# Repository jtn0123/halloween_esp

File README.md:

# Halloween Castle

A store-bought decorative castle with three lit apertures — two tower windows and
a doorway — driven by an ESP32-S3 Feather running ESPHome. Addressable RGBW pixels,
pre-rendered spooky audio, and a cue engine that keeps the two in step.

See [PROJECT_NOTES.md](PROJECT_NOTES.md) for the design record and the hardware
research behind every choice here — it is an index; the record itself lives in
parts under [`docs/notes/`](docs/notes/). The trust model — local-only, two
permanently accepted risks — is [docs/SECURITY.md](docs/SECURITY.md). For the night-to-night view —
adding a song end to end, pushing to the castle, what to check when a scene
will not play — see [docs/RUNBOOK.md](docs/RUNBOOK.md).

---

## How it fits together

```
scenes/scenes.yaml            ← THE SOURCE OF TRUTH
        │
        ├── tools/render_audio.py ─▶ core/ scene_render ─▶ audio/NN_<id>.mp3
        │                            (Rust: synths, reverb,   and audio/card/
        │                             master chain)            (the 96 kbps copies)
        ├── tools/gen_esphome.py  ──▶ audio/card/scenes/      (THE SHOW: show.man
        │                         │                            + one <id>.cue a scene)
        │                         └─▶ firmware/generated/     (sfx, rig.h, lights)
        └── tools/gen_previewer.py ─▶ previewer/castle-cue-desk.html (the desk)
```

One file defines every scene: its light cues, its audio score, its length and its
playback level. Everything else is generated. Cue timings tuned in the previewer
cannot drift away from the ones on the device, because both come from here.
Since v5.67 the show is card data, not firmware: one runner
(`firmware/castle_scenes.h`) reads `show.man` and the `.cue` files, so a scene
edit is `make publish`, never a flash.

`core/` is castle-core, the project's zero-dependency Rust crate. It renders the
scene audio (`scene_render`) and analyses imported tracks (`analyze_track`) —
those are the production paths, not experiments; the Python originals survive
only as the parity references the Rust is checked against. It also holds a
WASM face the cue desk loads and the studio server itself — the only one since
the Python studio retired on 2026-09-06 ([docs/RETIREMENT.md](docs/RETIREMENT.md)).
Everything else reaches the crate through
`tools/core_bins.py`, as a subprocess: no cargo means a hard stop with a
sentence, never a quiet fall-back to arithmetic that differs per machine.

### Why the audio is pre-rendered

The MAX98357A plays one stream, and mixing on the board itself is not worth
fighting (it was never an option at all on the single-core ESP32-S2 this show
was written for). So each scene is rendered offline into a single mixed file — where
convolution reverb, ducking and crossfades are free — and the firmware's only job
is to play it. This raises the quality ceiling rather than lowering it.

---

## Hardware

The [v3.4 Integrated PCB handoff](hardware/castle-carrier-v3.4/integrated/README.md)
contains its KiCad source, ENIG manufacturing review package, board images and QA evidence.
It remains an engineering prototype pending supplier and powered-board qualification.

| | |
|---|---|
| MCU | Adafruit ESP32-S3 Feather [#5477](https://www.adafruit.com/product/5477) — 240 MHz, 4 MB flash, 2 MB PSRAM, on castle-carrier v3.3a. An ESP32-S2 Feather ran the porch until 2026-09-17 ([docs/notes/03-build.md](docs/notes/03-build.md) §12.20) |
| Audio | MAX98357A I2S class-D amp ([adafruit 3006](https://www.adafruit.com/product/3006)) → 4 Ω speaker |
| Light | 2 × NeoPixel Jewel 7 RGBW (towers) + NeoPixel Ring 12 RGB (door) — three zones, 26 pixels; see [docs/WIRING.md](docs/WIRING.md) |
| Sensor | AM312 PIR on the walkway |

I2S and RMT are separate peripherals, so audio and pixels never contend for
hardware.

### Wiring

| Feather pin | GPIO | Goes to |
|---|---|---|
| A0 | 18 | 74AHCT125 → 470 Ω → Jewel `DIN` |
| A1 | 17 | AM312 PIR out |
| A3 | 15 | MAX98357A `DIN` |
| D11 | 11 | MAX98357A `BCLK` |
| D12 | 12 | MAX98357A `LRC` |
| USB | — | 5 V to amp, pixels, level shifter |
| GND | — | common ground |

**Why not D5/D6/D10, which would be the obvious choices?** History: until
v5.44 the microSD slot came on a 2.13" eInk FeatherWing, which hard-wires SD
chip select on D5, SRAM chip select on D6, eInk chip select on D9 and eInk
data/command on D10 — and putting 800 kHz NeoPixel data on the SD card's
chip select is not a mistake you find quickly. The wing and its status
panel are gone (the page does that job now), the carrier board's own card
socket kept D5, and D6/D10 went to the carrier's 5 V sense and wired button
instead. The signals stayed where they were soldered.

Put a 1000 µF capacitor across 5 V/GND at the pixels. With 26 pixels the
worst case (a full-white lightning strike) is ~2 A, so **split the 5 V supply
before the Feather** rather than drawing it all through its USB trace.

---

## Getting started

You need Python 3.13 and **a Rust toolchain** (`rustup`, which brings cargo).
`make setup` does not install Rust, and the step after it does not work
without one: `make audio` renders through castle-core and stops with a
sentence rather than falling back to Python. Node 22+, `lame` and `ffmpeg`
are needed for `make check`; `make setup` ends by naming whichever is missing,
with the command that installs it.

```bash
curl --proto '=https' --tlsv1.2 -sSf https://sh.rustup.rs | sh   # once
make setup      # venv from the hashed lock + web/ npm ci + the commit hook
make audio      # render the scene audio (builds core/ on first use)
make validate   # check the config without a toolchain
make build      # compile firmware/castle_feather_s3.yaml — the castle in the yard
make build-s3   # compile firmware/castle_s3.yaml — the ESP32-S3-WROOM-1 carrier
make build-fs3  # an alias for build; the castle IS the S3 Feather
make upload     # flash over USB
make publish    # push the rendered show to the castle's microSD card
```

Copy `firmware/secrets.yaml.example` to `firmware/secrets.yaml` and set real
WiFi credentials before flashing. `make help` lists every target.

There are two targets because there are two boards. `castle_feather_s3.yaml`
is the ESP32-S3 Feather (#5477, the 2 MB PSRAM one) in the castle-carrier
v3.3a the S2 was drawn for — it is the castle in the yard, and has run the
show since 2026-09-17. `castle_s3.yaml` (2026-09-05) is the
ESP32-S3-WROOM-1 carrier board (castle-carrier v5), written from that
project's spec with no board in hand; it has never been on hardware and is
compiled weekly by CI so it cannot rot. Both share every line of the show and
not one GPIO number differs between them — see `firmware/pending/README.md`
for what has run on what, and the bring-up list.

The scene audio lives on the card, not in the image — `make publish` is what
puts it there, and a board flashed without it chirps instead of playing. That
used to be a choice between two builds; the show's real songs weigh 2.2 MB
and an OTA slot holds 1.75 MB, so on 2026-09-01 the all-in-flash build was
retired and the card became the only way the castle plays (`docs/notes/03-build.md`
§12.15).

When both `site/index.html.gz` and `site/index.html` are on the card, `/`
serves the gzipped copy. `make publish` / `sd_sync site` writes both; a hand
copy must include the `.gz` or a newer plain file is ignored. A PUT whose
`Content-Length` is larger than the body that arrives is a known ESP-IDF
httpd limit (the socket closes on the short read). The API server has four
open sockets (`firmware/sd_web.h`); that is the board's pool, not a desk bug.

---

## Castle Radio on your desktop

Install it with `sh installer/install.sh` on an Apple Silicon Mac, or
`installer\install.cmd` on Windows ([installer/README.md](installer/README.md)):
it brings its own Python, ffmpeg and voice model, with no Homebrew. On a Mac,
double-click **Enable Website Startup.command** once, then use **Import
music → Start Castle Tools → Connect Castle Tools** on the castle website. The helper runs in the background without Terminal; keep the small
connection window open. Startup checks tools without installing anything. [Desktop setup and limitations](demo/castle-radio/README.md).

## The cue desk

```bash
make studio     # http://127.0.0.1:8765 — the previewer plus a local server
```

The previewer is one static HTML file (`previewer/castle-cue-desk.html`, built
by `make preview` from `web/src/`). Behind it, the studio server adds what a
static page cannot do: the **Tracks** panel imports audio (a file, or a link via
yt-dlp), shows onsets and waveforms, auditions clips, writes scenes into
`scenes/scenes.yaml`, and sends files to the castle's SD card when one answers.
`--lan` opens it to the phone/iPad remote; leave it off otherwise — a LAN
visitor has the whole desk, not a read-only view: they can import and delete
tracks, rewrite `scenes/scenes.yaml`, send files to the castle and stop the
server (`POST /studio/server/stop`), with no login. The route
table — what the studio owns (`/studio/…`) and what it relays to the castle
(`/api/…`) — is [docs/API.md](docs/API.md).

The studio is `core/src/bin/studio.rs`: `make studio` runs
`tools/studio_launch.sh`, which builds the binary when cargo is present and
execs it, and says why it cannot when there is no cargo and no build. There
was a second studio in Python until 2026-09-06, kept as the reference the
Rust one was measured against; [docs/RETIREMENT.md](docs/RETIREMENT.md) is
the plan that retired it and the tag `python-studio-final` is the last tree
carrying it. The server is Rust; the toolchain it spawns for every rebuild,
import and push is still Python, and that is the design rather than a
leftover — [docs/PARITY.md](docs/PARITY.md) says what is held equal to what.

Four environment variables sandbox it: `CASTLE_TRACKS` (track library
directory), `CASTLE_SCENES` (the scenes file it may write), `CASTLE_HOST`
(the castle's address; set-but-empty means "no castle") and `CASTLE_BUILD`
(where a rebuild's audio, generated firmware and previewer page land). The
tests set them so a run can never touch the real show. `tools/castle_emu.py 8093` plus
`CASTLE_HOST=127.0.0.1:8093` gives the whole desk→studio→castle chain with no
hardware at all.

---

## Development

```bash
make test       # python unit tests         make lint   # ruff + mypy
make check      # tests + lint + guards + tsc + node suites (what CI runs)
make e2e        # Playwright against the real studio (CASTLE_E2E_PORT=8821 to run two)
make coverage   # non-gating coverage report     make audit  # pip-audit, non-gating
```

The five implementations of the show's arithmetic (Python generators, TS
effects, C++ firmware, host-compiled dump, and castle-core in `core/`) are kept
bit-exact by seeded fuzz — [docs/PARITY.md](docs/PARITY.md) is the contract, the
list of every duplicated copy, and what to do when one of them goes red.
`make rust` builds the crate's binaries; `make rust-test` and `make rust-lint`
(fmt --check + clippy -D warnings) are the crate's own gates, and the same
checks ride inside `tests/test_castle_core.py` so `make check` covers `core/`
too — but only on a machine that has cargo and a host C++ compiler.
`make rust-coverage` is the crate's `cargo llvm-cov` summary, non-gating like
`make coverage`.

Every file is held to 500 lines (`tools/check_loc.py`, prose included).
`make setup` installs the commit hook (`git config core.hooksPath githooks`).
A git worktree needs its own `.venv` and `web/node_modules`, or symlinks back
to the main checkout's. The short version of all of this is
[CONTRIBUTING.md](CONTRIBUTING.md).

---

## Scenes

| Scene | Kind | Length | What happens |
|---|---|---|---|
| Vigil | ambient, loops | 30 s | Candles breathe, ember at the door, wind underneath |
| Storm | triggered | 6.5 s | Thunder first, strike 80 ms behind, rolling flashes |
| Séance | ambient, loops | 35 s | Organ procession i–♭II–i–V7♭9, violet with green wisps |
| Ballroom | ambient, loops | 15 s | Parlour waltz, music box over piano, violet↔green drift |
| Descent | showpiece | 27 s | 32′ pedal held throughout, chromatic descent, strikes on chord changes |
| Visitation | triggered | 11 s | Candles gutter out, cold green, eyes open in the left window |
| Approach | PIR | 8 s | Blackout, a beat of nothing, then the door blazes |
| Crypt | ambient, loops | 24 s | Heartbeat at 48 bpm, tritone drone, whispers; near-darkness is the effect |

Imported songs take the rest of the budget: the board holds **12 scenes**
(`SCENE_LIMIT` in `tools/check_loc.py`, and the desk refuses the thirteenth),
so the eight written above leave four slots for tracks brought in through the
Tracks panel, whose cues are onset-detected from the audio itself. Two of
those four are filled in `scenes/scenes.yaml` today.

All musical material written for the castle is original, written in the haunted-parlour idiom
(minor key, 3/4 or slow chords, raised 7th on the dominant). Nothing is a
transcription of an existing work.

### Effect vocabulary

`candle` · `ember` · `furnace` · `spirit` · `eyes` · `seance` · `wisp` ·
`mansion` · `chill` · `throb` · `strobe` · `off`, plus a global `strike` overlay.

Defined in [firmware/castle_effects.h](firmware/castle_effects.h). Flicker runs on
smoothed value noise, and the seed varies per pixel so flame moves *across* a
jewel rather than the whole window pulsing as one lamp.

---

## Safety

`Soften lightning` defaults **on**. Hard ~7 Hz white strobe sits in the
photosensitive seizure band, which matters for anything pointed at a public
walkway. Turning it off is a deliberate act. Since firmware v5.71 it acts on
flash TRAINS only: a strike is softened when it lands on a zone less than
333 ms after that same zone's previous strike (faster than three a second);
an isolated strike, or a steady beat on each fixture, lands at full strength.
The soft strobe effect is unchanged. The rule is `castle_layers.h`
`kSoftenWindowMs`, mirrored by the desk and the Radio (docs/PARITY.md).

---

## Licence

This repository's code is under the MIT License: see [LICENSE](LICENSE). A
built firmware image also contains GPL-3.0 components, ESPHome's C++ runtime
and esp-audio-libs, so an image is distributed as a whole under the GNU
General Public License version 3. [docs/LICENSING.md](docs/LICENSING.md) says
what each published artifact contains, under which terms, and where its
third-party notices are.

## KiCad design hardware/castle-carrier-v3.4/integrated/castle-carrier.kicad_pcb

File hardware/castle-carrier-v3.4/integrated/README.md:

# Castle v3.4 Integrated — Mac handoff

Open `castle-carrier.kicad_pro` with **KiCad 10.0.6 or newer KiCad 10**.
This is the Integrated N16R8 prototype: 16 MB flash, 8 MB octal PSRAM,
SD storage and directly mounted LEFT/RIGHT MAX98357A amplifiers.
The native PCB is authoritative; historical bootstrap scripts cannot recreate all final edits.

## Continue on another Mac

From a checkout of `jtn0123/halloween_esp`, run
`gh pr checkout pcb/v34-integrated-enig-handoff` or check out that remote branch with Git.
Open the project in `hardware/castle-carrier-v3.4/integrated/`.
Install the standard KiCad 10 symbols, footprints and 3D models, and initialize
its standard global library tables when prompted. Custom libraries and simplified
connector/button models are included. Project tables use KiCad environment variables
instead of the old USB application path.

Run `bash validate.sh` here for package integrity, ENIG agreement, the 16-hole list,
fresh DRC with schematic parity and ERC. Set `KICAD_CLI` if KiCad is outside
`/Applications/KiCad/KiCad.app` and not on PATH. Reports go to ignored `local-checks/`.
This focused check does not reproduce the original two-variant engineering QA suite.

## Manufacturing decision

- ENIG, 1 microinch gold; four layers, 1.6 mm FR-4 TG135;
  1 oz outer / 0.5 oz inner copper.
- Exactly 16 epoxy-filled, planarized, copper-capped thermal holes:
  12 beneath the ESP32 module and two beneath each amplifier.
- JLC Standard assembly and X-ray; five boards, two assembled and three bare.
- Red or black remains an order choice. Intended supply: regulated 5 V / 4 A
  barrel adapter. The board is 100 × 80 mm.

Read [assembly notes](ASSEMBLY-NOTES.md) and
[current requirements](docs/ASSEMBLY-REQUIREMENTS.md).
Unzip [the manufacturing package](out/DFM_REVIEW_NOT_RELEASED.zip) and read
`READ-ME-FIRST.md`. It contains Gerbers, drills, engineering BOM, a placement
reference and the thermal-hole map. It remains **review only, not released**;
placement data and CAD paste layers require assembler approval.

## Current readiness

The October 7 follow-up fixes the clean-checkout validator, refreshes Integrated compilation against application commit 3078e35, and tunes both USB-C contact paths to about 0.795 mm mismatch (target <=1 mm). The revised native PCB passed refilled DRC/parity with no violations or disconnected items. The 100 x 80 mm outline, component placement, finish and 16-hole process stay the same.

C20/C21/C24/C25 now select Samsung CL10C221JB8NNNC / C27675 after comparing electrical specs and dimensions with the out-of-stock Murata part. The engineering BOM and manufacturing ZIP agree. [Stock evidence](qa/jlc-stock-20261007.json) is a dated public-page snapshot, not reserved inventory. The fuse cartridge remains a separately installed exact-MPN item.

See [readiness findings](docs/READINESS-20261007.md), [dimensioned fit drawing](out/fit-dimensions.pdf), [supplier review request](docs/SUPPLIER-REVIEW.md), and [first-board procedure](docs/FIRST-ARTICLE-TEST.md). The only given mechanical constraint is the 80-82 mm PCB-width cap; no enclosure model is assumed. The RF clearance outside the PCB is not a component body.

The [firmware overlay](firmware-reference/castle_v34.yaml) now has a [portable compilation workflow](firmware-reference/README.md), with [current build evidence](qa/firmware-build-20261007.json). Compilation is not physical playback or detected-memory proof. Printed v3.3a keeps its existing mono profile.

The archived receipt `20261002T012938Z-df738972` describes the earlier USB workspace and is historical; it does not qualify the revised USB copper or current application firmware. Keep [the archive](qa/20261002T012938Z-df738972-evidence.zip) and [ENIG source patch](qa/enig-source-update.patch) as history. The new report records fresh checks separately. The portable import manifest hashes published files, excluding KiCad local settings.

Supplier CAM/stock/orientation/stencil acceptance and powered USB, stereo, SD, combined-load/thermal and RF tests remain open. This is a prototype handoff, not a production release. No order, supplier submission, device flash or physical test was performed.

## Board views

These are CAD images. Component positions remain unchanged; current copper views include the USB correction.

More top, bottom, angled, schematic and mechanical views are in `renders/` and `out/`.

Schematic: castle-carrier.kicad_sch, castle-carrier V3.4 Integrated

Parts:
C1, C2, C6, C11, C14, C17, C18, C22: 100nF; C_0603_1608Metric
C3: 10uF 16V; CP_Radial_D6.3mm_P2.50mm
C4: 1000uF 16V; CP_Radial_D10.0mm_P5.00mm
C5: 470uF 16V; CP_Radial_D8.0mm_P3.50mm
C7, C8, C19, C23: 10uF 25V; C_0805_2012Metric
C9, C10, C13: 22uF 25V; C_0805_2012Metric
C15: 1uF; C_0603_1608Metric
C16, C26: 1uF 25V; C_0805_2012Metric
C20, C21, C24, C25: 220pF; C_0603_1608Metric
D1: SS56C; D_SMC
D3: SMBJ6.8A; D_SMB
D4: amber; LED_1206_3216Metric
D5: 12V zener; D_SOD-123
D6, D7: B5819W; D_SOD-123
F1: 4A 5x20; Fuseholder_5x20_BLX-A
FB1, FB2, FB3, FB4: BLM21PG221SN1D; L_0805_2012Metric
H1, H2, H3, H4: M3; MountingHole_3.2mm_M3
J1, J2, J3, J4: PT 3.5 1x03; TerminalBlock_Phoenix_PT-1,5-3-3.5-H_1x03_P3.50mm_Horizontal
J5: AM312 PIR; JST_XH_B3B-XH-A_1x03_P2.50mm_Vertical
J7: SPEAKER L; TerminalBlock_Phoenix_PT-1,5-2-3.5-H_1x02_P3.50mm_Horizontal
J8: SPEAKER R; TerminalBlock_Phoenix_PT-1,5-2-3.5-H_1x02_P3.50mm_Horizontal
J9: DM3AT-SF-PEJM5; microSD_HC_Hirose_DM3AT-SF-PEJM5
J10: DEBUG UART; PinHeader_1x05_P2.54mm_Vertical
J11: DC-005-5A; DC-005
J12: BTN + PIXEL; JST_XH_B4B-XH-A_1x04_P2.50mm_Vertical
J15: QWIIC I2C; JST_SH_SM04B-SRSS-TB_1x04-1MP_P1.00mm_Horizontal
J16: TYPE-C-31-M-12; USB_C_Receptacle_HRO_TYPE-C-31-M-12
L1: 4.7uH; L_Sunlord_SWPA6045S
Q1: AOD4185; TO-252-3_TabPin2
R1, R2, R3, R4: 100R; R_1206_3216Metric
R5, R6, R7, R8, R9, R10, R11: 10k; R_1206_3216Metric
R12: 4k7; R_Axial_DIN0207_L6.3mm_D2.5mm_P7.62mm_Horizontal
R13: 10k; R_Axial_DIN0207_L6.3mm_D2.5mm_P7.62mm_Horizontal
R14, R17, R18, R31, R32: 10k; R_0603_1608Metric
R19: 100R; R_0603_1608Metric
R20: 1k; R_0603_1608Metric
R21: 10mR; R_2512_6332Metric
R22, R23: 5k1; R_0603_1608Metric
R24, R25: 4k7; R_0603_1608Metric
R26, R27, R28: 33R; R_0603_1608Metric
R29: 100k; R_0603_1608Metric
R30: 374k; R_0603_1608Metric
SW1: OS102011MS2Q; SW_Slide_SPDT_CK_OS102011MS2Q
SW2: BOOT; SW_Push_1P1T_XKB_TS-1187A
SW3: RESET; SW_Push_1P1T_XKB_TS-1187A
TP1: +5V; TestPoint_Pad_D1.5mm
TP2: +3V3; TestPoint_Pad_D1.5mm
TP3: GND; TestPoint_Pad_D1.5mm
TP4: TOWERL; TestPoint_Pad_D1.5mm
TP5: DOOR; TestPoint_Pad_D1.5mm
TP6: TOWERR; TestPoint_Pad_D1.5mm
TP7: SPARE; TestPoint_Pad_D1.5mm
TP8: VBUS; TestPoint_Pad_D1.5mm
U1: 74AHCT125; SOIC-14_3.9x8.7mm_P1.27mm
U2: ESP32-S3-WROOM-1-N16R8; ESP32-S3-WROOM-1
U3: AP63203WU-7; TSOT-23-6
U4: USBLC6-2SC6; SOT-23-6
U5: INA219AIDCNR; SOT-23-8
U6, U7: MAX98357AETE+T; MAX98357A_TQFN16_3x3
U8: TPS22919DCKR; SOT-363_SC-70-6

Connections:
+3V3: C2.1, C3.1, C7.1, C9.1, C10.1, C13.1, C14.1, C17.1, J5.1 (3V3), J9.4 (VDD), J15.2 (3V3), L1.2, R5.1, R6.1, R7.1, R13.1, R17.1, R18.1, R24.1, R25.1, R31.1, R32.1, TP2.1, U2.2 (3V3), U3.1 (FB), U5.4 (VS), U5.7 (A0)
+5V: C1.1, C4.1, C5.1, C18.1, C19.1, C22.1, C23.1, D1.1 (K), D3.1 (K), D7.2 (A), J1.1 (5V), J2.1 (5V), J3.1 (5V), J4.1 (5V), J10.1 (5V), J12.1 (5V), R12.1, R21.2 (OUT), R29.1, R30.1, TP1.1, U1.14 (VCC), U5.2 (IN-), U6.7 (VDD), U6.8 (VDD), U7.7 (VDD), U7.8 (VDD)
/AUD_L_MODE: R29.2, U6.4 (SD_MODE)
/AUD_L_N: FB2.1, U6.10 (OUTN)
/AUD_L_P: FB1.1, U6.9 (OUTP)
/AUD_L_SPK_N: C21.1, FB2.2, J7.2 (SPK-)
/AUD_L_SPK_P: C20.1, FB1.2, J7.1 (SPK+)
/AUD_R_MODE: R30.2, U7.4 (SD_MODE)
/AUD_R_N: FB4.1, U7.10 (OUTN)
/AUD_R_P: FB3.1, U7.9 (OUTP)
/AUD_R_SPK_N: C25.1, FB4.2, J8.2 (SPK-)
/AUD_R_SPK_P: C24.1, FB3.2, J8.1 (SPK+)
/BOOT0: R18.2, SW2.1, U2.27 (IO0)
/BST_BUCK: C11.1, U3.6 (BST)
/CC1: J16.A5 (CC1), R22.1
/CC2: J16.B5 (CC2), R23.1
/GATE_P: D5.2 (A), Q1.1 (G), R14.1
/LED_A: D4.2 (A), SW1.1 (A)
/PWR_LED: R12.2, SW1.2 (B)
/RST_BTN: R19.1, SW3.2
/RST_J10: J10.5 (RST), R20.1
/SHUNT_5V: D5.1 (K), Q1.3 (S), R21.1 (IN), U5.1 (IN+)
/SW_BUCK: C11.2, L1.1, U3.5 (SW)
/VIN_F: F1.2, Q1.2 (D)
/VIN_RAW: F1.1, J11.1 (CENTRE_+)
/Y1: R1.2, U1.3 (1Y)
/Y2: R2.2, U1.6 (2Y)
/Y3: R3.2, U1.8 (3Y)
/Y4: R4.2, U1.11 (4Y)
BTN: C6.1, J12.3 (BTN), R13.2, U2.18 (IO10)
CHIP_EN: C15.1, R17.2, R20.2, SW3.1, U2.3 (EN)
DBG_RX: J10.3 (RX), U2.36 (RXD0)
DBG_TX: J10.4 (TX), U2.37 (TXD0)
DOOR: J2.3 (DATA), R2.1, TP5.1
DOOR_3V3: R9.1, U1.5 (2A), U2.9 (IO16)
GND: C1.2, C2.2, C3.2, C4.2, C5.2, C6.2, C7.2, C8.2, C9.2, C10.2, C13.2, C14.2, C15.2, C16.2, C17.2, C18.2, C19.2, C20.2, C21.2, C22.2, C23.2, C24.2, C25.2, C26.2, D1.2 (A), D3.2 (A), D4.1 (K), J1.2 (GND), J2.2 (GND), J3.2 (GND), J4.2 (GND), J5.3 (GND), J9.6 (VSS), J9.SH (SHIELD), J10.2 (GND), J11.2 (SLEEVE), J11.3 (SW), J12.2 (GND), J15.1 (GND), J15.MP, J16.A1 (GND), J16.A12 (GND), J16.B1 (GND), J16.B12 (GND), J16.SH (SHIELD), R8.2, R9.2, R10.2, R11.2, R14.2, R19.2, R22.2, R23.2, SW2.2, TP3.1, U1.1 (1OE), U1.4 (2OE), U1.7 (GND), U1.10 (3OE), U1.13 (4OE), U2.1 (GND), U2.40 (GND), U2.41 (EPAD), U3.4 (GND), U4.2 (GND), U5.3 (GND), U5.8 (A1), U6.3 (GND), U6.11 (GND), U6.15 (GND), U6.17 (EP), U7.3 (GND), U7.11 (GND), U7.15 (GND), U7.17 (EP), U8.2 (GND)
I2S_BCLK: R26.1, U2.19 (IO11)
I2S_BCLK_A: R26.2, U6.16 (BCLK), U7.16 (BCLK)
I2S_DIN: R28.1, U2.8 (IO15)
I2S_DIN_A: R28.2, U6.1 (DIN), U7.1 (DIN)
I2S_LRC: R27.1, U2.20 (IO12)
I2S_LRC_A: R27.2, U6.14 (LRCLK), U7.14 (LRCLK)
PIR_OUT: J5.2 (OUT), U2.10 (IO17)
SCL: J15.4 (SCL), R25.2, U2.38 (IO2), U5.5 (SCL)
SDA: J15.3 (SDA), R24.2, U2.39 (IO1), U5.6 (SDA)
SD_CS: J9.2 (CD/DAT3), R5.2, U2.5 (IO5)
SD_DAT1: J9.8 (DAT1), R32.2
SD_DAT2: J9.1 (DAT2), R31.2
SD_MISO: J9.7 (DAT0), R7.2, U2.34 (IO41)
SD_MOSI: J9.3 (CMD), R6.2, U2.32 (IO39)
SD_SCK: J9.5 (CLK), U2.33 (IO40)
SPARE: J4.3 (DATA), J12.4 (DAT), R4.1, TP7.1
SPARE_3V3: R11.1, U1.12 (4A), U2.12 (IO8)
TOWERL: J1.3 (DATA), R1.1, TP4.1
TOWERL_3V3: R8.1, U1.2 (1A), U2.11 (IO18)
TOWERR: J3.3 (DATA), R3.1, TP6.1
TOWERR_3V3: R10.1, U1.9 (3A), U2.22 (IO14)
USB_DM: J16.A7 (D-), J16.B7 (D-), U2.13 (USB_D-), U4.3 (I/O2), U4.4 (I/O2)
USB_DP: J16.A6 (D+), J16.B6 (D+), U2.14 (USB_D+), U4.1 (I/O1), U4.6 (I/O1)
USB_SOFT: D6.2 (A), U8.6 (OUT)
VBUCK: C8.1, D6.1 (K), D7.1 (K), U3.2 (EN), U3.3 (VIN)
VBUS: C16.1, C26.1, J16.A4 (VBUS), J16.A9 (VBUS), J16.B4 (VBUS), J16.B9 (VBUS), TP8.1, U4.5 (VBUS), U8.1 (IN), U8.3 (ON)

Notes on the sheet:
POWER J11 -> F1 -> VIN_F; D1 clamp + D3 TVS + C4 on the protected +5V
POWER INDICATOR +5V -> R12 -> SW1 -> D4
MODULE SUPPLY the datasheet's own C1 = 22uF and C3 = 100nF at U2 pin 2
BOOT / RESET / EN NO CAP EVER ON BOOT0
DEBUG 3V3 UART, 5 V on PIN 1, EN via R20
TEST POINTS bare 1.5 mm pads, probe from the top
LEVEL SHIFT + ZONES 3.3 V in, 5 V out, 100R in series
STORAGE microSD, SPI, REQUIRED
SENSOR + I2C AM312 PIR, and J15 for a Qwiic device beside the on-board sensor
BUTTON wired switch on D10 + one pixel on SPARE
3V3 D6 / D7 OR USB VBUS and the barrel into VBUCK; U3 makes the ONE 3.3 V rail from it
AMMETER R21 10mOhm in series in the 5 V trunk, U5 across it at 0x41, and the I2C pull-ups
USB native, no bridge chip: two CC pull-downs, a USBLC6-2SC6 the pair passes THROUGH, 1uF VBUS
AUDIO: two on-board MAX98357A; LEFT / RIGHT stereo; 9 dB; floating speaker outputs
PROTECT: Q1 permanently in series; no bypass; 5 V supply ONLY
MCU: ESP32-S3-WROOM-1-N16R8; 16 MB flash / 8 MB octal PSRAM
I2S: 33R source damping; not a power isolation device
USB STARTUP: controlled rise; QOD disabled; D6 blocks barrel backfeed
SD: unused DAT1 / DAT2 require 10k pull-ups too
v3.4 engineering prototype - NOT RELEASED FOR MANUFACTURE
5 V center-positive supply only. TVS is not a DC overvoltage cutoff.
No speaker terminal may connect to ground or another output.
USB powers logic only; lights and amplifiers require barrel supply.

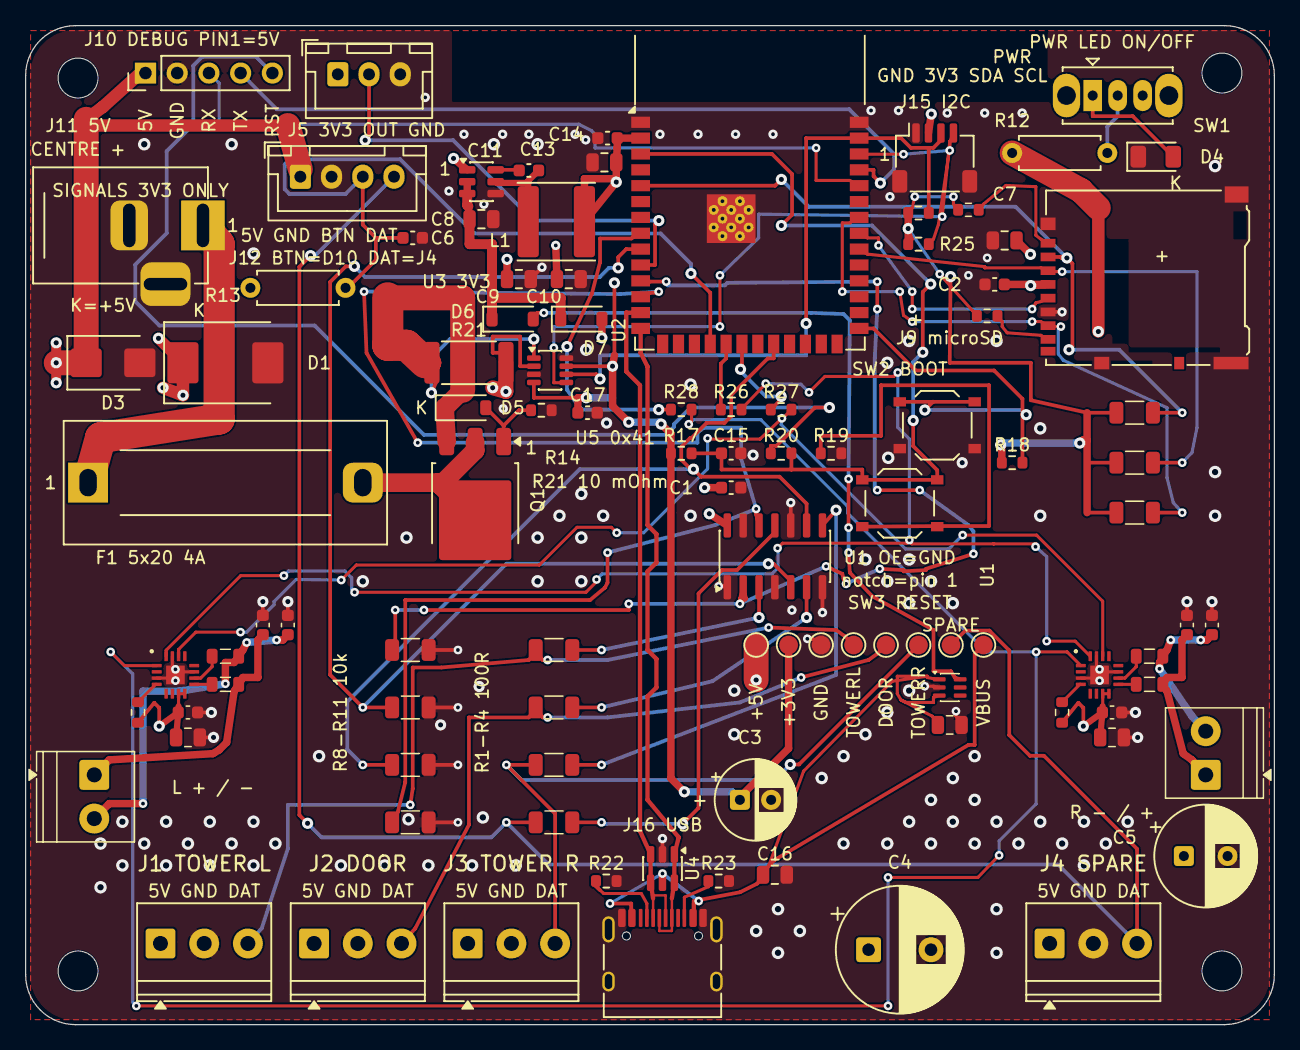
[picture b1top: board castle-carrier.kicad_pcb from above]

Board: 4 copper layers, 100.0 x 80.0 mm, 104 parts (0 on the bottom side), 62 nets.

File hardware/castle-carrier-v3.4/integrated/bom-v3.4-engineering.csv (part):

Reference,Value / MPN,Footprint,LCSC part,Sourcing status,Manufacturer,Selected MPN,Requirements,Source
U2,ESP32-S3-WROOM-1-N16R8,castle:ESP32-S3-WROOM-1,C2913202,"Exact MPN selected; source by MPN, no unreviewed substitutions",Espressif,ESP32-S3-WROOM-1-N16R8,16 MB flash / 8 MB octal PSRAM; module exposed-pad process per fabrication notes; matching Integrated firmware required,https://www.espressif.com/sites/default/files/documentation/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
U1,74AHCT125,castle:SOIC-14_3.9x8.7mm_P1.27mm,C155176,Inherited v5 selection; reconfirm before ordering,,,,
J1,PT 3.5 1x03,"TerminalBlock_Phoenix:TerminalBlock_Phoenix_PT-1,5-3-3.5-H_1x03_P3.50mm_Horizontal",C474893,Inherited v5 selection; reconfirm before ordering,,,,
J2,PT 3.5 1x03,"TerminalBlock_Phoenix:TerminalBlock_Phoenix_PT-1,5-3-3.5-H_1x03_P3.50mm_Horizontal",C474893,Inherited v5 selection; reconfirm before ordering,,,,
J3,PT 3.5 1x03,"TerminalBlock_Phoenix:TerminalBlock_Phoenix_PT-1,5-3-3.5-H_1x03_P3.50mm_Horizontal",C474893,Inherited v5 selection; reconfirm before ordering,,,,
J4,PT 3.5 1x03,"TerminalBlock_Phoenix:TerminalBlock_Phoenix_PT-1,5-3-3.5-H_1x03_P3.50mm_Horizontal",C474893,Inherited v5 selection; reconfirm before ordering,,,,
R1,100R,Resistor_SMD:R_1206_3216Metric,C137392,"Exact MPN selected; source by MPN, no unreviewed substitutions",Yageo,RC1206FR-07100RL,"100 ohm, 1%, 1206, 0.25 W at 70 C",https://www.yageogroup.com/component-documentation/download/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
R2,100R,Resistor_SMD:R_1206_3216Metric,C137392,"Exact MPN selected; source by MPN, no unreviewed substitutions",Yageo,RC1206FR-07100RL,"100 ohm, 1%, 1206, 0.25 W at 70 C",https://www.yageogroup.com/component-documentation/download/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
R3,100R,Resistor_SMD:R_1206_3216Metric,C137392,"Exact MPN selected; source by MPN, no unreviewed substitutions",Yageo,RC1206FR-07100RL,"100 ohm, 1%, 1206, 0.25 W at 70 C",https://www.yageogroup.com/component-documentation/download/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
R4,100R,Resistor_SMD:R_1206_3216Metric,C137392,"Exact MPN selected; source by MPN, no unreviewed substitutions",Yageo,RC1206FR-07100RL,"100 ohm, 1%, 1206, 0.25 W at 70 C",https://www.yageogroup.com/component-documentation/download/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
R8,10k,Resistor_SMD:R_1206_3216Metric,C132649,"Exact MPN selected; source by MPN, no unreviewed substitutions",Yageo,RC1206FR-0710KL,"10 kohm, 1%, 1206, 0.25 W at 70 C",https://www.yageogroup.com/component-documentation/download/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
R9,10k,Resistor_SMD:R_1206_3216Metric,C132649,"Exact MPN selected; source by MPN, no unreviewed substitutions",Yageo,RC1206FR-0710KL,"10 kohm, 1%, 1206, 0.25 W at 70 C",https://www.yageogroup.com/component-documentation/download/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
R10,10k,Resistor_SMD:R_1206_3216Metric,C132649,"Exact MPN selected; source by MPN, no unreviewed substitutions",Yageo,RC1206FR-0710KL,"10 kohm, 1%, 1206, 0.25 W at 70 C",https://www.yageogroup.com/component-documentation/download/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
R11,10k,Resistor_SMD:R_1206_3216Metric,C132649,"Exact MPN selected; source by MPN, no unreviewed substitutions",Yageo,RC1206FR-0710KL,"10 kohm, 1%, 1206, 0.25 W at 70 C",https://www.yageogroup.com/component-documentation/download/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
C1,100nF,castle:C_0603_1608Metric,C14663,Inherited v5 selection; reconfirm before ordering,,,,
C5,470uF 16V,Capacitor_THT:CP_Radial_D8.0mm_P3.50mm,C1579437,Inherited v5 selection; reconfirm before ordering,,,,
R26,33R,castle:R_0603_1608Metric,C108661,"Exact MPN selected; source by MPN, no unreviewed substitutions",Yageo,RC0603FR-0733RL,"33 ohm, 1%, 0603, 0.1 W",https://www.yageogroup.com/component-documentation/download/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
R27,33R,castle:R_0603_1608Metric,C108661,"Exact MPN selected; source by MPN, no unreviewed substitutions",Yageo,RC0603FR-0733RL,"33 ohm, 1%, 0603, 0.1 W",https://www.yageogroup.com/component-documentation/download/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
R28,33R,castle:R_0603_1608Metric,C108661,"Exact MPN selected; source by MPN, no unreviewed substitutions",Yageo,RC0603FR-0733RL,"33 ohm, 1%, 0603, 0.1 W",https://www.yageogroup.com/component-documentation/download/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
J9,DM3AT-SF-PEJM5,Connector_Card:microSD_HC_Hirose_DM3AT-SF-PEJM5,C114218,"Exact MPN selected; source by MPN, no unreviewed substitutions",Hirose,DM3AT-SF-PEJM5,MicroSD push/push socket; native footprint; installed-height and insertion/ejection fit remain physical gates,https://www.hirose.com/product/p/CL0609-0031-0-00
R5,10k,Resistor_SMD:R_1206_3216Metric,C132649,"Exact MPN selected; source by MPN, no unreviewed substitutions",Yageo,RC1206FR-0710KL,"10 kohm, 1%, 1206, 0.25 W at 70 C",https://www.yageogroup.com/component-documentation/download/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
R6,10k,Resistor_SMD:R_1206_3216Metric,C132649,"Exact MPN selected; source by MPN, no unreviewed substitutions",Yageo,RC1206FR-0710KL,"10 kohm, 1%, 1206, 0.25 W at 70 C",https://www.yageogroup.com/component-documentation/download/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
R7,10k,Resistor_SMD:R_1206_3216Metric,C132649,"Exact MPN selected; source by MPN, no unreviewed substitutions",Yageo,RC1206FR-0710KL,"10 kohm, 1%, 1206, 0.25 W at 70 C",https://www.yageogroup.com/component-documentation/download/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
C2,100nF,castle:C_0603_1608Metric,C14663,Inherited v5 selection; reconfirm before ordering,,,,
C7,10uF 25V,castle:C_0805_2012Metric,C15850,"Exact MPN selected; source by MPN, no unreviewed substitutions",Samsung,CL21A106KAYNNNE,"10 uF 25 V X5R 0805; assess effective capacitance at bias, tolerance and temperature; nominal capacitance is not proof",https://product.samsungsem.com/mlcc/CL21A106KAYNNN.do
C3,10uF 16V,Capacitor_THT:CP_Radial_D6.3mm_P2.50mm,C2835646,Inherited v5 selection; reconfirm before ordering,,,,
J5,AM312 PIR,Connector_JST:JST_XH_B3B-XH-A_1x03_P2.50mm_Vertical,C144394,Inherited v5 selection; reconfirm before ordering,,,,
J12,BTN + PIXEL,Connector_JST:JST_XH_B4B-XH-A_1x04_P2.50mm_Vertical,C144395,Inherited v5 selection; reconfirm before ordering,,,,
R13,10k,Resistor_THT:R_Axial_DIN0207_L6.3mm_D2.5mm_P7.62mm_Horizontal,C5618323,Inherited v5 selection; reconfirm before ordering,,,,
C6,100nF,castle:C_0603_1608Metric,C14663,Inherited v5 selection; reconfirm before ordering,,,,
J10,DEBUG UART,castle:PinHeader_1x05_P2.54mm_Vertical,C492404,Inherited v5 selection; reconfirm before ordering,,,,
J15,QWIIC I2C,castle:JST_SH_SM04B-SRSS-TB_1x04-1MP_P1.00mm_Horizontal,C160404,Inherited v5 selection; reconfirm before ordering,,,,
J11,DC-005-5A,castle:DC-005,C381116,Inherited v5 selection; reconfirm before ordering,,,,
F1,4A 5x20,castle:Fuseholder_5x20_BLX-A,C3131,"Exact MPN selected; source by MPN, no unreviewed substitutions",Xucheng,5x20 BLX-A XC-7,"Holder only, rated 6.3 A; fit one separately listed F1-CARTRIDGE",https://www.lcsc.com/product-detail/C3131.html
D1,SS56C,castle:D_SMC,C24138,Inherited v5 selection; reconfirm before ordering,,,,
Q1,AOD4185,castle:TO-252-3_TabPin2,C400894,Inherited v5 selection; reconfirm before ordering,,,,
R14,10k,castle:R_0603_1608Metric,C25804,Inherited v5 selection; reconfirm before ordering,,,,
D5,12V zener,castle:D_SOD-123,C500776,Inherited v5 selection; reconfirm before ordering,,,,
C4,1000uF 16V,Capacitor_THT:CP_Radial_D10.0mm_P5.00mm,C2166071,Inherited v5 selection; reconfirm before ordering,,,,
D3,SMBJ6.8A,castle:D_SMB,C152090,Inherited v5 selection; reconfirm before ordering,,,,
U3,AP63203WU-7,castle:TSOT-23-6,C780769,"Exact MPN selected; source by MPN, no unreviewed substitutions",Diodes Incorporated,AP63203WU-7,"Fixed 3.3 V buck; 2 A component rating, not an assembled-board rating; TSOT26",https://www.diodes.com/assets/Datasheets/AP63200-AP63201-AP6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
L1,4.7uH,castle:L_Sunlord_SWPA6045S,C78804,"Exact MPN selected; source by MPN, no unreviewed substitutions",Sunlord,SWPA6045S4R7MT,"4.7 uH +/-20%; 6.0 +/-0.3 mm body, 4.5 mm max height; 34 milliohm max DCR; catalog Isat 4.97 A / Irms 3.30 A (columns headed Max); board current/thermal qualification remains open",https://www.sunlordinc.com/uploads/files/20221122/SWPA%20ser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

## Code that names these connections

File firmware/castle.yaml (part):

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  # renumbers nothing else. docs/WIRING.md §1-2. A2 and A4 were the pins left
  # free beside the eInk wing; GPIO16 is safe for the same reason GPIO15 is —
  # this board fits no 32 kHz crystal.
  pin_towerL: "18"      # A0  -> 74AHCT125 1Y -> 470R -> tower L DIN
  pin_door: "16"        # A2  -> 74AHCT125 2Y -> 470R -> doorway DIN
  pin_towerR: "14"      # A4  -> 74AHCT125 3Y -> 470R -> tower R DIN
  # Pixel count and colour type per zone. These MUST agree with the `zones:`
  # block in scenes/scenes.yaml — that is what the cue scripts and the
  # geometry tables in generated/rig.h were built against.
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  channels_door: "GRB"
  pin_pir: "17"         # A1  <- AM312 PIR out (3V3 logic)
  pin_i2s_dout: "15"    # A3  -> MAX98357A DIN
  pin_i2s_bclk: "11"    # D11 -> MAX98357A BCLK   (clear of the wing)
  pin_i2s_lrclk: "12"   # D12 -> MAX98357A LRC    (clear of the wing)
  # Both amps sit on those same three wires; the second one costs no GPIO.
  # docs/WIRING.md §5.
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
